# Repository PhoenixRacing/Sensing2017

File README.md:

# Olin College of Engineering Baja Electrical Subteam Repository

## Backbox

Contains the back-end files (.ino) for the various Arduinos responsible for communication and various tasks relating to reading in sensor data and passing it to the dashboard and SD card.

## Dashboard

Contains the files (.ino) necessary for communicating between the dashboard Arduino and the backbox, as well as for displaying information to the driver as well as logging the information the SD card.

## Dependencies

Contains the libraries necessary to making the code compile on the Arduinos.

## Examples

Contains example code for the various components of the electrical subsystem (refer to system architecture diagram); utilize this for reference for skeleton code.

## LogFiles

Contains (or will contain) the log files saved on the SD card from the car. Will either be in .csv or.xlsx format.

## Outdated Code

Contains archival code from past years that has been ommitted for various reasons (didn't work, redone, unnecessary).

## i2cSlaveTest

Will be absorbed underneath Examples directory eventually. Contains example code for a test for communication between two Arduinos over i2c.

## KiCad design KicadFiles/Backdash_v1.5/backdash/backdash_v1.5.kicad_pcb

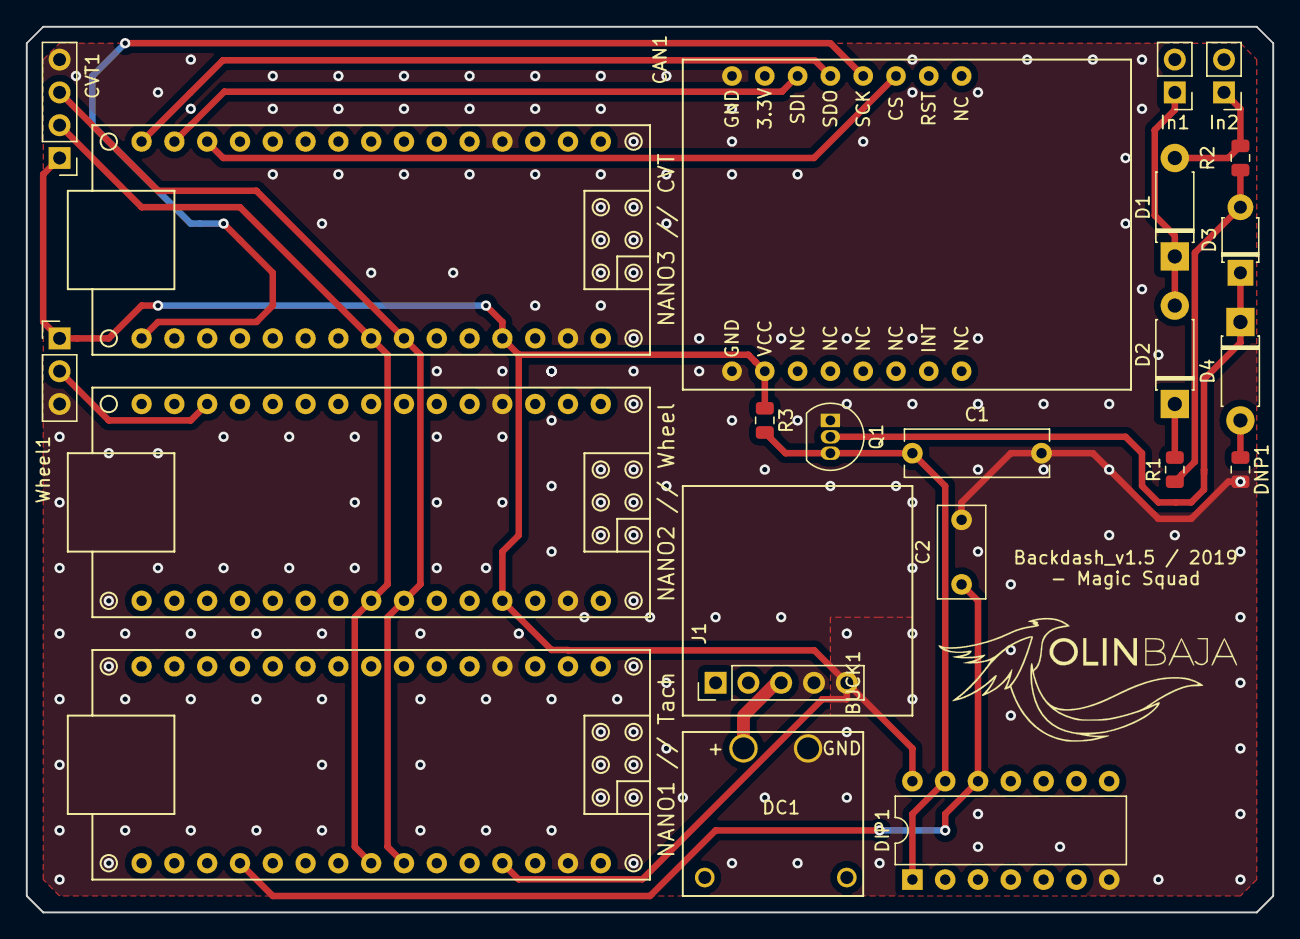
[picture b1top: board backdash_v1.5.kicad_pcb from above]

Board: 2 copper layers, 96.5 x 68.6 mm, 22 parts (0 on the bottom side), 19 nets.

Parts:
BUCK1: Conn_01x05_Female; Buck_module
C1: 2200pF; C_Rect_L11.0mm_W3.5mm_P10.00mm_MKT
C2: 39nF; C_Rect_L7.0mm_W3.5mm_P5.00mm
CAN1: Conn_01x16_Female; CAN_Module
CVT1: Conn_01x04_Female; PinHeader_1x04_P2.54mm_Vertical
D1, D2: 1N4007; D_DO-41_SOD81_P7.62mm_Horizontal
D3: 1N4148; D_T-1_P5.08mm_Horizontal
D4: 1N4738; D_DO-41_SOD81_P7.62mm_Horizontal
DC1: Conn_01x04_Female; DC_Connector
DIP1: SN74HC14N; DIP-14_W7.62mm
DNP1: DNP; R_0805_2012Metric
In1: Vin +; PinHeader_1x02_P2.54mm_Vertical
In2: Vin-; PinHeader_1x02_P2.54mm_Vertical
NANO1 // Tach, NANO2 // Wheel, NANO3 // CVT: Conn_01x30_Female; arduino_nano
Q1: 2N3904; TO-92_Inline
R1, R2: 10k; R_0805_2012Metric
R3: 4.7k; R_0805_2012Metric
Wheel1: Conn_01x03_Female; PinHeader_1x03_P2.54mm_Vertical

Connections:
/+: BUCK1.3, DC1.2
/A0: C2.1, DIP1.12, NANO1 // Tach.19
/A4: CVT1.2, NANO1 // Tach.23, NANO2 // Wheel.23, NANO3 // CVT.23
/A5: CVT1.3, NANO1 // Tach.24, NANO2 // Wheel.24, NANO3 // CVT.24
/CS: CAN1.6, NANO3 // CVT.13
/D10: NANO2 // Wheel.13, Wheel1.2
/GND: BUCK1.4, C1.2, C2.2, CAN1.1, CAN1.16, CVT1.4, DC1.1, DIP1.7, DNP1.2, NANO1 // Tach.4, NANO1 // Tach.29, NANO2 // Wheel.4, NANO2 // Wheel.29, NANO3 // CVT.4, NANO3 // CVT.29, Q1.1, Wheel1.3
/RST: CAN1.7, NANO1 // Tach.3, NANO1 // Tach.28, NANO2 // Wheel.3, NANO2 // Wheel.28, NANO3 // CVT.3, NANO3 // CVT.28
/SCK: CAN1.5, NANO3 // CVT.16
/SDI: CAN1.3, NANO3 // CVT.14
/SDO: CAN1.4, NANO3 // CVT.15
/VCC: BUCK1.5, CAN1.15, CVT1.1, DIP1.14, NANO1 // Tach.27, NANO2 // Wheel.27, NANO3 // CVT.27, R3.1, Wheel1.1
unnamed: C1.1, DIP1.1, DIP1.13, Q1.3, R3.2
unnamed: D1.1, D2.2, In1.1
unnamed: D1.2, In2.1, R2.1
unnamed: D2.1, R1.2
unnamed: D3.1, D4.1, Q1.2
unnamed: D3.2, R1.1, R2.2
unnamed: D4.2, DNP1.1

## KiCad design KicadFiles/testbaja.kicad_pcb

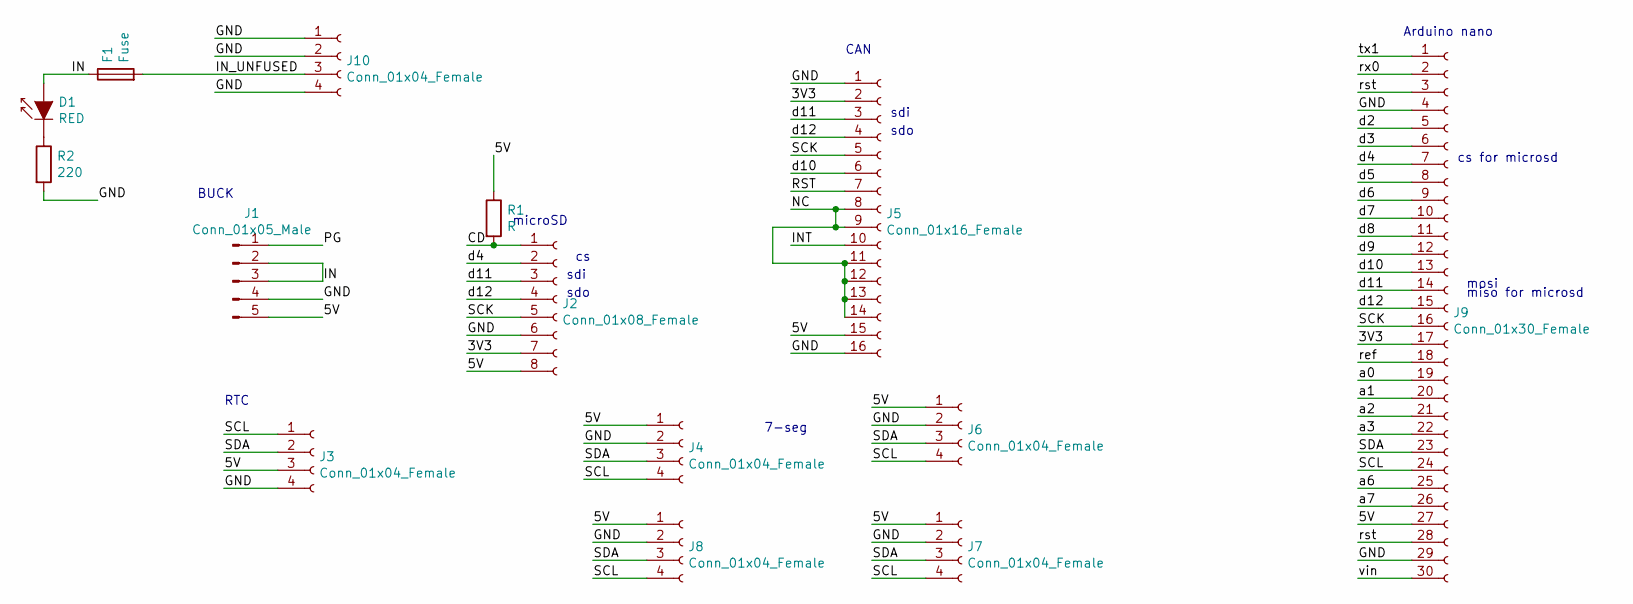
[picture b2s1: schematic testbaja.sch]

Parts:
D1: RED; LED_D5.0mm_FlatTop
F1: Fuse; Fuse_0ZCFSeries
J1: Conn_01x05_Male; Buck_module
J2: Conn_01x08_Female; microSD_module
J3: Conn_01x04_Female; RealTimeClock
J4, J6, J7, J8: Conn_01x04_Female; 7_segment_display
J5: Conn_01x16_Female; CAN_Module
J9: Conn_01x30_Female; arduino_nano
J10: Conn_01x04_Female; DC_Connector
R1: R; R_1206_3216Metric_Pad1.42x1.75mm_HandSolder
R2: 220; R_0805_2012Metric

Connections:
/3V3: J2.7, J5.2, J9.17
/5V: J1.5, J2.8, J3.3, J4.1, J5.15, J6.1, J7.1, J8.1, J9.27, R1.1
/CD: J2.1, R1.2
/GND: J1.4, J2.6, J3.4, J4.2, J5.1, J5.16, J6.2, J7.2, J8.2, J9.4, J9.29, J10.1, J10.2, J10.4, R2.2
/IN: D1.2 (A), F1.1, J1.2, J1.3
/INT: J5.10
/IN_UNFUSED: F1.2, J10.3
/NC: J5.8, J5.9, J5.11, J5.12, J5.13, J5.14
/PG: J1.1
/RST: J5.7
/SCK: J2.5, J5.5, J9.16
/SCL: J3.1, J4.4, J6.4, J7.4, J8.4, J9.24
/SDA: J3.2, J4.3, J6.3, J7.3, J8.3, J9.23
/a0: J9.19
/a1: J9.20
/a2: J9.21
/a3: J9.22
/a6: J9.25
/a7: J9.26
/d2: J9.5
/d3: J9.6
/d4: J2.2, J9.7
/d5: J9.8
/d6: J9.9
/d7: J9.10
/d8: J9.11
/d9: J9.12
/d10: J5.6, J9.13
/d11: J2.3, J5.3, J9.14
/d12: J2.4, J5.4, J9.15
/ref: J9.18
/rst: J9.3, J9.28
/rx0: J9.2
/tx1: J9.1
/vin: J9.30
unnamed: D1.1 (K), R2.1

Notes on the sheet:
microSD
BUCK
RTC
7-seg
CAN
Arduino nano
cs for microsd
miso for microsd
mosi
sdi
sdo

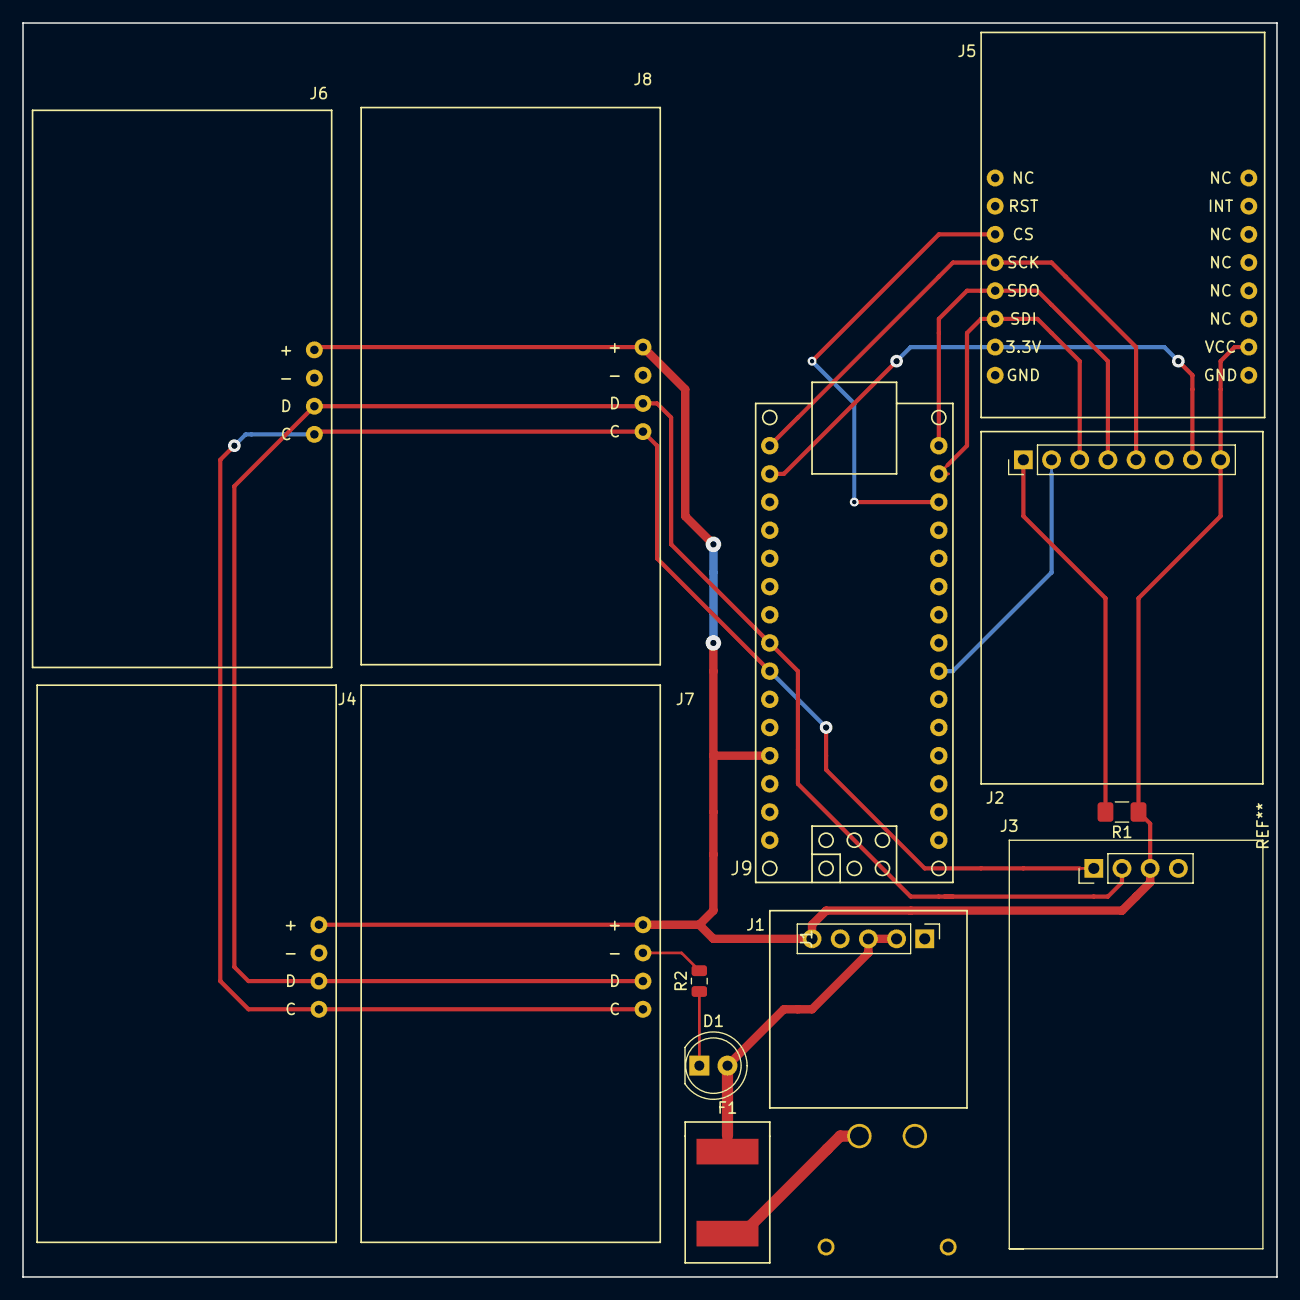
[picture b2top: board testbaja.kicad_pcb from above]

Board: 2 copper layers, 113.0 x 113.0 mm, 14 parts (1 on the bottom side), 16 nets.

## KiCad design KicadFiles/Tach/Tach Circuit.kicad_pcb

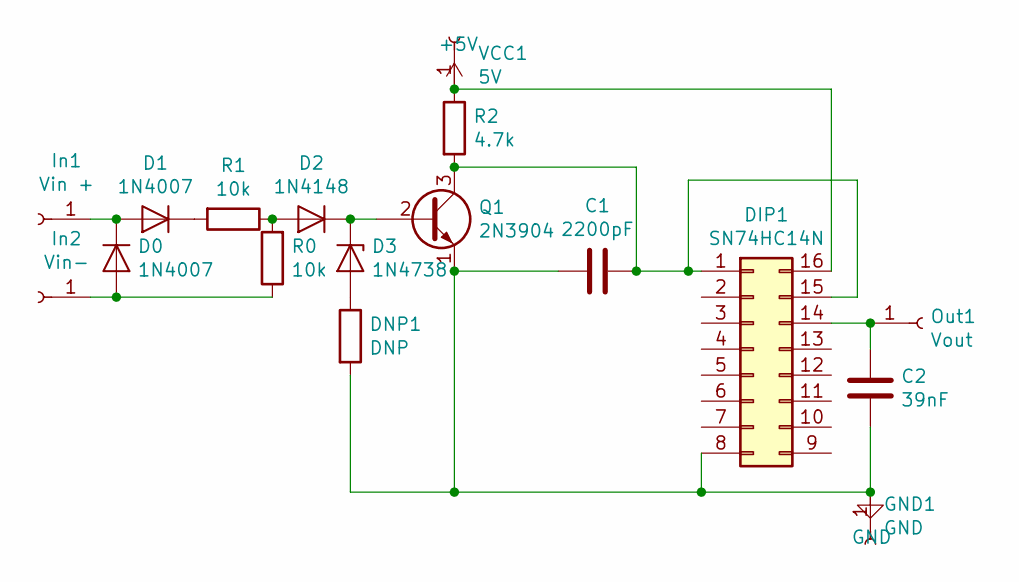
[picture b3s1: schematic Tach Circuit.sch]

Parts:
C1: 2200pF; C_Rect_L11.0mm_W3.5mm_P10.00mm_MKT
C2: 39nF; C_Rect_L7.0mm_W3.5mm_P5.00mm
D0, D1: 1N4007; D_DO-41_SOD81_P7.62mm_Horizontal
D2: 1N4148; D_T-1_P5.08mm_Horizontal
D3: 1N4738; D_DO-41_SOD81_P7.62mm_Horizontal
DIP1: SN74HC14N; DIP-16_W7.62mm
DNP1: DNP; R_0805_2012Metric
GND1: GND; PinHeader_1x02_P2.54mm_Vertical
In1: Vin +; PinHeader_1x02_P2.54mm_Vertical
In2: Vin-; PinHeader_1x02_P2.54mm_Vertical
Out1: Vout; PinHeader_1x02_P2.54mm_Vertical
Q1: 2N3904; TO-92_Inline
R0, R1: 10k; R_0805_2012Metric
R2: 4.7k; R_0805_2012Metric
VCC1: 5V; PinHeader_1x02_P2.54mm_Vertical

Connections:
+5V: DIP1.16, R2.1, VCC1.1
GND: C1.2, C2.2, DIP1.8, DNP1.2, GND1.1, Q1.1 (E)
unnamed: C1.1, DIP1.1, DIP1.15, Q1.3 (C), R2.2
unnamed: C2.1, DIP1.14, Out1.1
unnamed: D0.1 (K), D1.2 (A), In1.1
unnamed: D0.2 (A), In2.1, R0.1
unnamed: D1.1 (K), R1.2
unnamed: D2.1 (K), D3.1 (K), Q1.2 (B)
unnamed: D2.2 (A), R0.2, R1.1
unnamed: D3.2 (A), DNP1.1

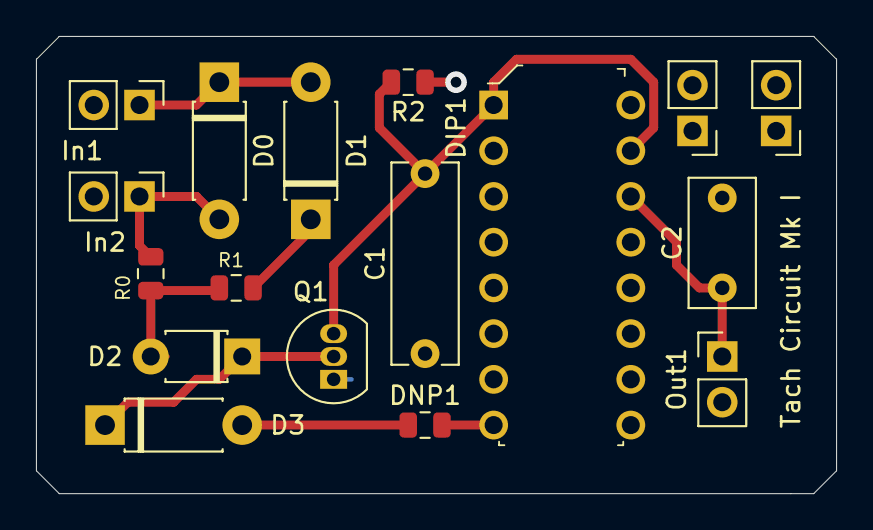
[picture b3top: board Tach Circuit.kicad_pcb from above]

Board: 2 copper layers, 44.4 x 25.4 mm, 17 parts (0 on the bottom side), 10 nets.

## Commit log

2017-10-20 Add rolling average example code and i2c example code
2017-10-25 Add tachometer average code
2017-10-25 Fix folder formatting
2017-10-25 Create frequencyCode_informalRollingAverage
2017-10-25 Add hall effect sensor
2017-10-26 12c scanning code from online
2017-10-26 frequency sender and receiver compile but not tested
2017-10-27 add seven segment test code
2017-10-27 i2c frequency sampling, averaging, and sending working!
2017-11-01 Adds integration between i2c and 77
2017-11-01 change addresses
2017-11-02 Added example log files
2017-11-08 RTC code
2017-11-15 Add CVT heat sensing
2017-11-17 "Added pointers"
2017-11-29 Add code for thermocoupler
2017-11-29 Add reading of RTC
2017-12-01 clean up dash computer code
2017-12-01 Clean up dash code: compiles but not tested
2017-12-02 add startup to dash display
2017-12-03 Logger fully functional and integrated with rtc
2017-12-06 commented out log button
2017-12-08 Init commit
2017-12-08 Fixed a few things
2017-12-08 Added request event
2017-12-08 renamed request_event
2018-01-27 created moving average library
2018-01-27 added example and library
2018-02-09 data logger not working
2018-02-20 CAN click TX and RX, not working fully.
2018-02-20 it works now. buf is the data
2018-02-21 CAN working with ints
2018-03-09 rtd sensor code to integrate later
2018-03-09 "dash info displaying properly, SD card still having write problems"
2018-03-13 Got CAN to spit over RTD values.
2018-03-13 commented on status, changed to unsigned ints
2018-03-28 "got sd logger working"
2018-04-11 "added CAN to dash and logging"
2018-04-11 fixed dash delay problem, reimplemented logger, cleaned up
2018-04-13 back dash
2018-04-17 commented out i2c sections to see how the can section is doing
2018-04-18 worked on i2c to can
2018-04-20 Started to parse i2c data
2018-04-23 Almost go the whole chain going
2018-04-24 fix spi-can bridge arduino and spi slave
2018-04-24 Worked on back dash
2018-04-30 "for 4/30"
2018-05-01 I2c sending rtd values
2018-05-01 I2c of rtd works, plus some functionality in freq tester
2018-05-04 tach sending all the way through
2018-05-04 missed a file from last commit
2018-05-07 Cleaned up repo
2018-05-08 IR sensor sending thru can to dashboard
2018-05-08 getting it to send two at once
2018-05-08 sending multiple messages from one node working in TEMP. Frequency integration started but not working for mph
2018-05-11 "trying to commit"
2018-05-11 uh merge plz
2018-05-11 got the wrong merge lmao
2018-05-11 Changing a weird merge and also freq
2018-05-11 maybe this will work
2018-09-26 RTC Footprint
2018-09-26 Footprint for Arduino Nano
2018-09-26 created 7 segment display footprint
2018-09-28 CAN module footprint v1
2018-10-03 half done making a board
2018-10-12 DC connector
2018-10-12 all routed
2018-10-16 all file update before i install ubuntu
2018-10-17 Routing needed
2018-10-18 ground = poured
2018-10-19 hopefully this works
2018-10-19 ORDERED BOARDS
2018-10-31 New and improved and still in progress
2018-11-02 backdash schematic
2018-11-02 backdash footprints assigned
2018-11-07 update backdash
2018-11-09 bmp to footprint
2018-11-09 Added logo and fixed connectors
2018-11-09 large
2018-11-09 sized for tach
2018-11-09 front dash with specific circuitry
2018-11-14 Labels added
2018-11-14 need to add in power
2018-11-14 Started the circuitry for the backdash version 2
2018-11-14 logo and batt added
2018-11-14 Starting ATMEGA
2018-11-16 nano progress made
2018-11-24 Board edge was a little off
2018-11-24 Adding all the gerber files
2018-11-28 Added can circuitry
2018-11-30 nano completed
2018-12-05 mini sd card code, might even be the same as the sd card code
2018-12-05 Front dash mini sd card is almost done
2018-12-05 started back dash
2019-02-01 Fixed frontdash can CS
2019-02-13 fixed error codes
2019-02-13 more errors!
2019-02-22 un-deleted schematic
2019-02-22 added tach sechematic, needs buck footprint
2019-02-22 pcb is once again messy
2019-02-27 updating backdash
2019-02-27 Removed RTD, fixed schematic, added tach, looks pretty
2019-03-06 gerbers exist now
2019-03-06 labeled nanos
2019-03-06 oops un-deleted logo
2019-03-06 yeet gerbers added for real this time
2019-03-13 this should hopefully be readable by china
2019-03-27 fixed gerbers correctly this time I hope
2019-03-27 hope pcbway likes this one
2020-02-26 added gitignore for unzipped dependencies
